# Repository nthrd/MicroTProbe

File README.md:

MicroTProbe
===========

A breakout for the [TMP102] [1] from Texas Instruments small enough to fit inside a ¼ inch copper tube. This was inspired by the [SparkFun breakout board] [2] for the same chip.

This is designed to be used with 1/4 inch copper tube and thermal putty to create a water-sealed temperature probe. Instead of using a header to hookup, magnet wire is threaded through the holes and soldered. Using a solderable magnet wire is recommended.

Source Files are a KiCAD project.

[1]: http://www.ti.com/product/tmp102 (Product Page)
[2]: https://www.sparkfun.com/products/11931 (SparkFun Breakout Board for TMP102)

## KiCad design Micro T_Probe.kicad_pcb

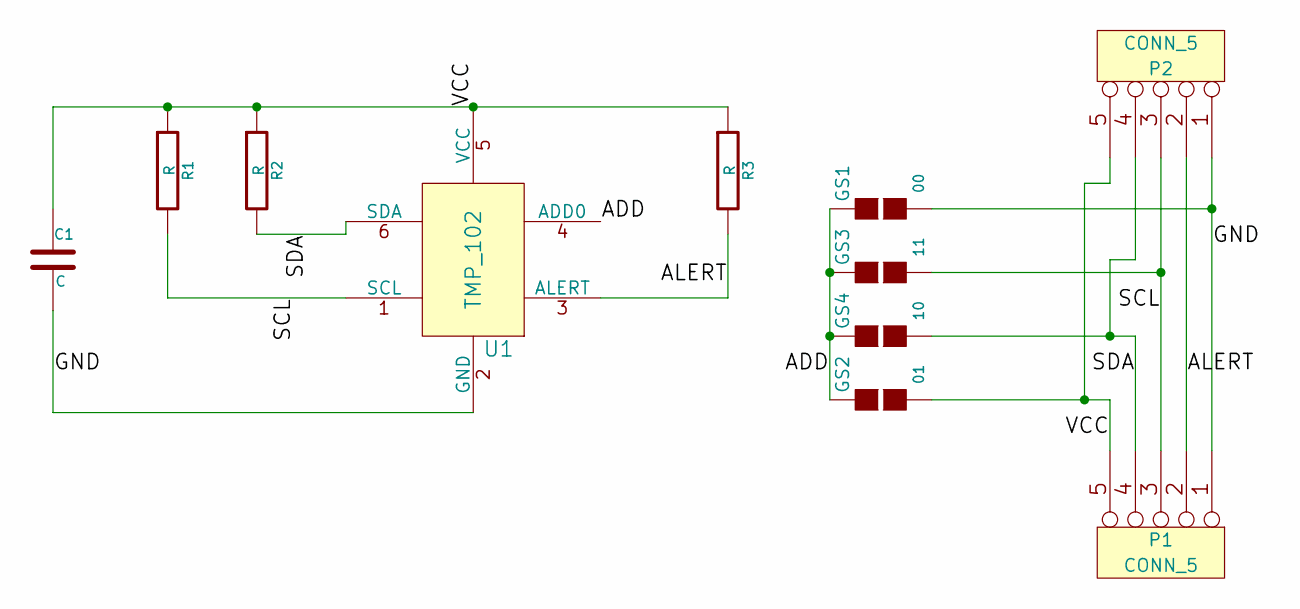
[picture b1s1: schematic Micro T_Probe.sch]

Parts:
C1: C
GS1: 00
GS2: 01
GS3: 11
GS4: 10
P1, P2: CONN_5
R1, R2, R3: R
U1: TMP_102

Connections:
/ADD: GS1.1 (G1), GS2.1 (G1), GS3.1 (G1), GS4.1 (G1), U1.4 (ADD0)
/ALERT: P1.2, P2.2, R3.2, U1.3 (ALERT)
/GND: C1.2, GS1.2 (G2), P1.1, P2.1, U1.2 (GND)
/SCL: GS3.2 (G2), P1.3, P2.3, R1.2, U1.1 (SCL)
/SDA: GS4.2 (G2), P1.4, P2.4, R2.2, U1.6 (SDA)
/VCC: C1.1, GS2.2 (G2), P1.5, P2.5, R1.1, R2.1, R3.1, U1.5 (VCC)

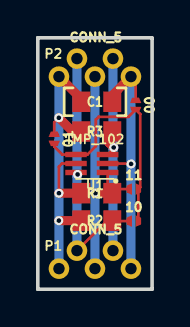
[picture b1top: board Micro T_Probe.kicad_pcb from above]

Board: 2 copper layers, 6.4 x 14.0 mm, 11 parts (0 on the bottom side), 6 nets.

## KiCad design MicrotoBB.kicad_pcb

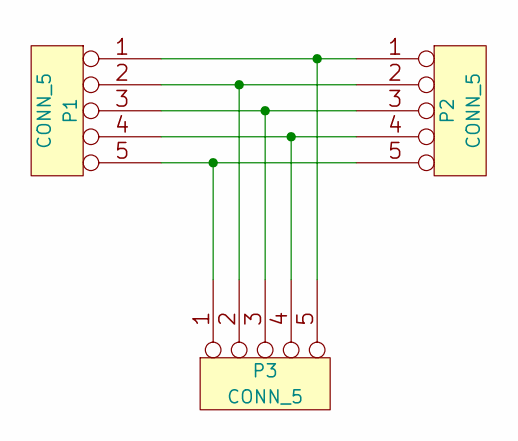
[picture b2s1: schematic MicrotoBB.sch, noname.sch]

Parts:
P1, P2, P3: CONN_5

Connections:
unnamed: P1.3, P2.3, P3.3
unnamed: P1.4, P2.4, P3.4
unnamed: P1.2, P2.2, P3.2
unnamed: P1.5, P2.5, P3.1
unnamed: P1.1, P2.1, P3.5

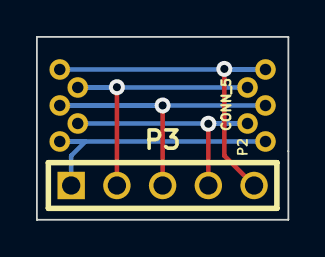
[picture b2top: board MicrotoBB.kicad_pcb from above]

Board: 2 copper layers, 14.0 x 10.2 mm, 3 parts (1 on the bottom side), 5 nets.

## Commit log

2014-07-09 Added more description.
2014-07-09 Switched to CC-BY-SA for hardware project.
2014-07-09 First commit with files
2014-08-03 Updated the solderability of this board by removing the mask above the solder junctions and enlarging the pads.
